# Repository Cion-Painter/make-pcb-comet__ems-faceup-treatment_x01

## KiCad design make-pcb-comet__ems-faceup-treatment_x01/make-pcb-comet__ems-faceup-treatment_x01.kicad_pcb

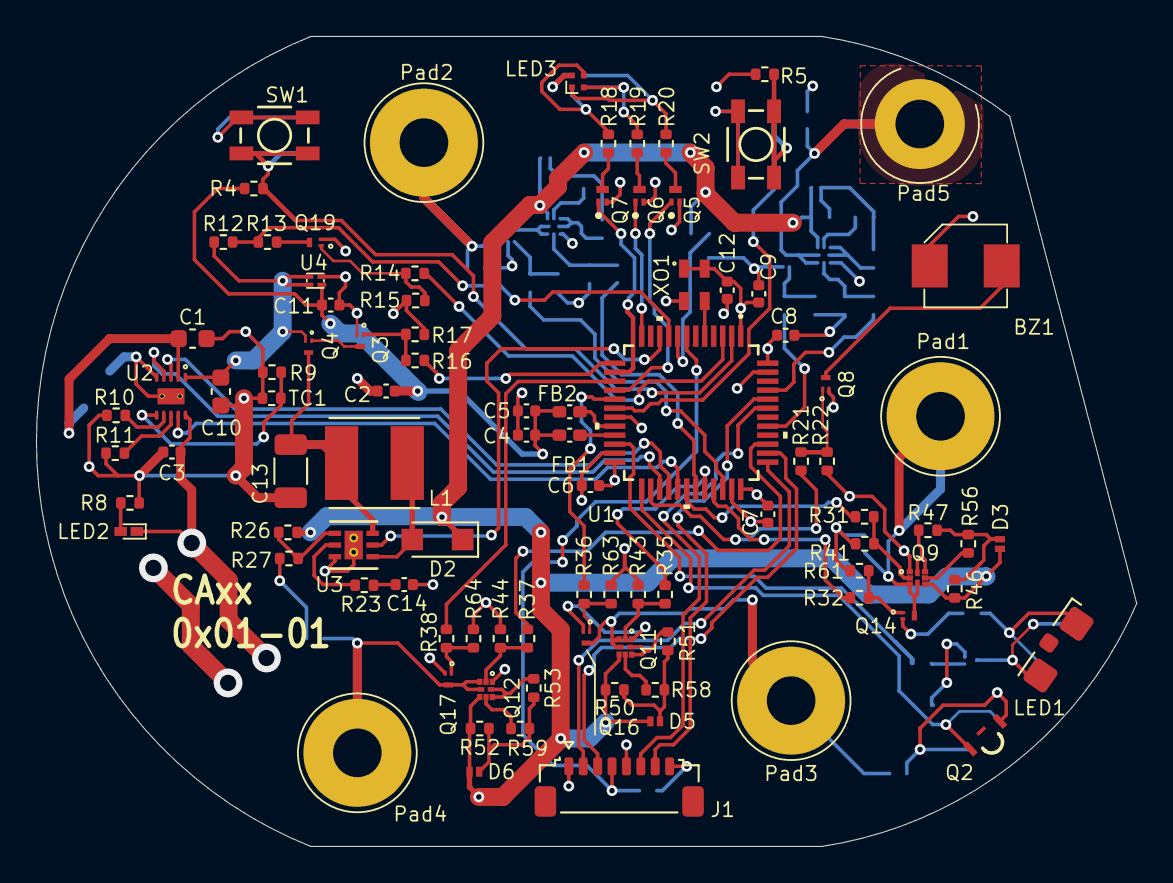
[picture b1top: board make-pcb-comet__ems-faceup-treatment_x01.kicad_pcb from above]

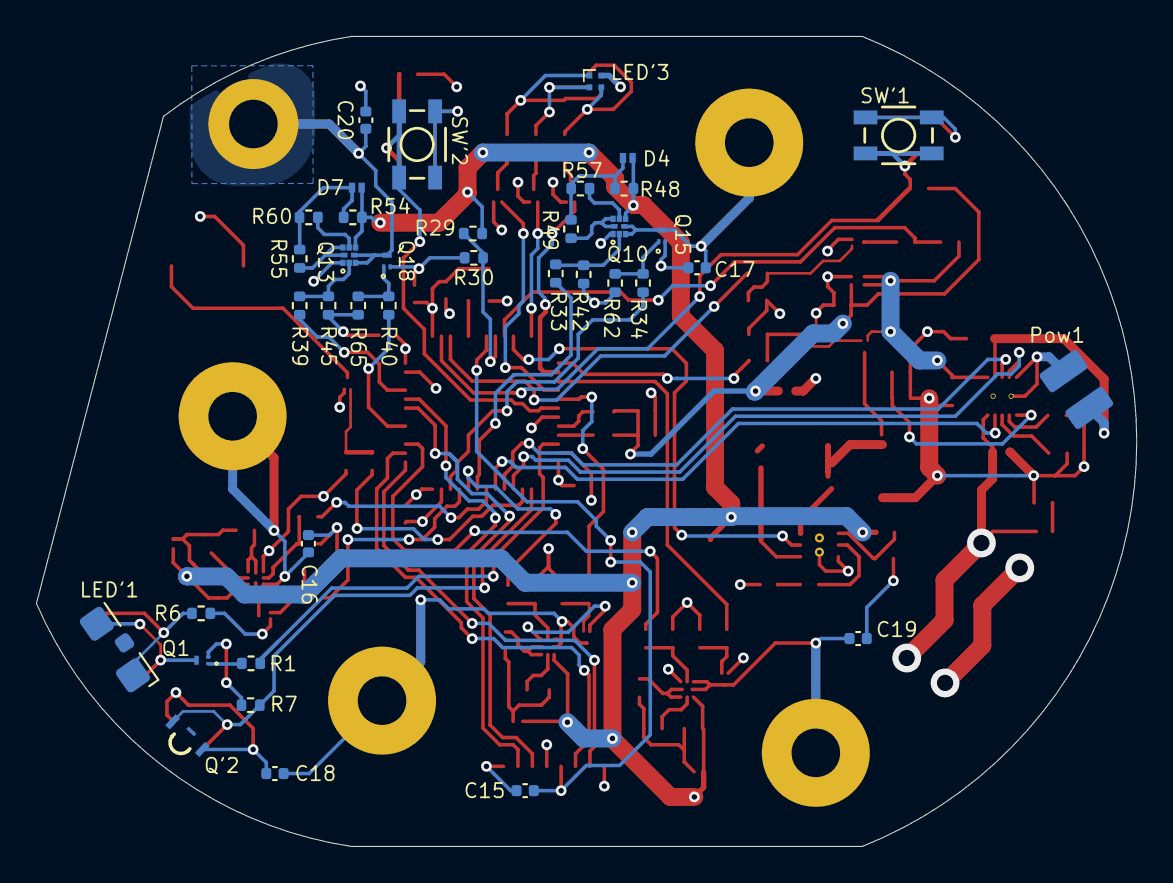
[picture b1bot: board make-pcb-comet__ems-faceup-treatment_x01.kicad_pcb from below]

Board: 4 copper layers, 61.1 x 45.0 mm, 132 parts (38 on the bottom side), 94 nets.

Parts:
BZ1: OWMB-404020SA-40-17; 4.0x4.0 SP OWMB-404020SA
C1: 4.7uF; C_0603_1608Metric
C2: 4.7uF; C_0402_1005Metric
C3, C9, C11: 1uF; C_0402_1005Metric
C4, C5, C6, C7, C8, C12, C15, C16, C17, C18, C19, C20: 0.1uF; C_0402_1005Metric
C10: 10uF; C_0603_1608Metric
C13: 10uF; C_1206_3216Metric
C14: 33nF; C_0402_1005Metric
D2: SS16FP; Nexperia_CFP3_SOD-123W
D3, D4, D5, D6, D7: PZU5.1BL; SOD-882_TOS
FB1, FB2: BLM15AG601SN1D; L_0402_1005Metric_Pad0.77x0.64mm_HandSolder
J1: SUH_Connector_side_08-pin; JST_SUR_SM08B-SURS-TF_1x08-1MP_P0.80mm_Horizontal
L1: LQH5BPN100MT0L; IND_LQH5BPN100MT0L
LED1: KPA-3010F3C; LED_Kingbright_KPA-3010_3x2x1mm
LED2: KPHHS-1005SURCK; LED_APHHS1005
LED3: UHD111A-FKA-C3K23E1L3VG5ZB3Z3; SMD4_UHD111A-FKA_CRW
LED'1: LED_Kingbright_KPA-3010_3x2x1mm
LED'3: UHD111A-FKA-C3K23E1L3VG5ZB3Z3; SMD4_UHD111A-FKA_CRW
Pad1, Pad2, Pad3, Pad4, Pad5: Pad 6 _ Hole 3.5
Pow1: LiPo 3.2 x 1.7
Q1, Q4: CSD25483F4; YJC0003A_TEX
Q2: 1541021NCA170; WL-STSB_1002
Q3, Q8, Q14, Q15, Q16, Q17, Q18, Q19: RV2E014AJ; DFN1006
Q5, Q6, Q7: DDTC143ZLP; DFN101X61X53-3N
Q9, Q10, Q11, Q12, Q13: PMCXB1000UE; TRANS_PMDXB600UNEZ
Q'2: 1541021NCA170; WL-STSB_1002
R1, R14, R16, R21, R31, R32, R33, R34, R35, R36, R37, R38, R39, R40, R47, R49, R51, R53, R55: 100; R_0402_1005Metric
R4, R5, R7: 51k; R_0402_1005Metric
R6: 68; R_0402_1005Metric
R8: 470; R_0402_1005Metric
R9, R12: 10k; R_0402_1005Metric
R10, R13: 3.3k; R_0402_1005Metric
R11: 33k; R_0402_1005Metric
R15, R17, R22, R41, R42, R43, R44, R45, R61, R62, R63, R64, R65: 100k; R_0402_1005Metric
R18, R19, R20: 300; R_0402_1005Metric
R23: 36.5k; R_0402_1005Metric
R26: 187k; R_0402_1005Metric
R27: 10.5k; R_0402_1005Metric
R29: 510k; R_0402_1005Metric
R30: 62k; R_0402_1005Metric
R46, R48, R50, R52, R54: 47k; R_0402_1005Metric
R56, R57, R58, R59, R60: 22; R_0402_1005Metric
SW1, SW2: EVPAA; SW_EVP-AA102K_PAN
SW'1, SW'2: EVPAA; SW_EVP-AA102K_PAN
TC1: NTC; R_0402_1005Metric
U1: STM32G431C6T6; LQFP48-7x7mm
U2: BQ25185DLHR; IC_BQ25185DLHR
U3: TPS61170DRVRG4; 6-WDFN_roshutsu_DRV6_1P6X1
U4: XC6504A3317R-G; USPN-4B02
XO1: SG2016CAN20.0000M-TJGA3; SMT_M-TJGA3_EPS

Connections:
+USB_5V0: C3.1, LED2.1 (Anode), U2.10 (IN)
/BAT_VOL: R12.2, R13.2, U1.9 (PA1)
/Buzz: R21.2, U1.26 (PB12)
/EMC_Pow: R16.1, U1.13 (PA5)
/EMS(1)_H: R31.1, U1.30 (PA8)
/EMS(1)_L: R32.1, U1.33 (PA11)
/EMS(2)_H: R33.1, U1.31 (PA9)
/EMS(2)_L: R34.1, U1.34 (PA12)
/EMS(3)_H: R35.1, U1.32 (PA10)
/EMS(3)_L: R36.1, U1.17 (PB1)
/EMS(4)_H: R37.1, U1.39 (PA15)
/EMS(4)_L: R38.1, U1.15 (PA7)
/EMS(5)_H: R39.1, U1.45 (PB8-BOOT0)
/EMS(5)_L: R40.1, U1.41 (PB4)
/EMS_POW: R29.1, R30.2, U1.8 (PA0)
/EMS_POW_PWM: U1.10 (PA2), U3.5 (CTRL)
/EMS_SW: R4.1, SW1.3 (K), SW1.4 (A), SW'1.3 (K), SW'1.4 (A), U1.2 (PC13)
/IrD_RX: Q2.1 (C), Q'2.1 (C), R7.1, U1.25 (PB11)
/IrD_TX: R1.1, U1.22 (PB10)
/LEDB: Q5.1 (B), U1.16 (PB0)
/LEDG: Q6.1 (B), U1.12 (PA4)
/LEDR: Q7.1 (B), U1.14 (PA6)
/RESET_SW: C15.2, J1.4, U1.7 (PG10-NRST)
/SW1: R5.1, SW2.3 (K), SW2.4 (A), SW'2.3 (K), SW'2.4 (A), U1.18 (PB2)
/SWCLK: J1.3, U1.38 (PA14)
/SWDIO: J1.2, U1.37 (PA13)
/UART1_RX: J1.7, U1.44 (PB7)
/UART1_TX: J1.6, U1.43 (PB6)
EMS_Pow_20V: D2.1 (K), D3.1 (Cathode), D4.1 (Cathode), D5.1 (Cathode), D6.1 (Cathode), D7.1 (Cathode), Q9.4 (Source2), Q10.4 (Source2), Q11.4 (Source2), Q12.4 (Source2), Q13.4 (Source2), R26.2, R29.2, R46.2, R48.2, R50.2, R52.2, R54.2
GNDPWR: C1.2, C2.1, C3.2, C4.1, C5.1, C6.1, C7.1, C8.1, C9.1, C10.2, C11.2, C12.1, C13.2, C14.2, C15.1, C16.1, C17.1, C18.1, C19.1, C20.1, J1.1, J1.8, Pow1.2 (-), Q2.2 (E), Q3.2 (Source), Q5.2 (E), Q6.2 (E), Q7.2 (E), Q8.2 (Source), Q9.1 (Source1), Q10.1 (Source1), Q11.1 (Source1), Q12.1 (Source1), Q13.1 (Source1), Q14.2 (Source), Q15.2 (Source), Q16.2 (Source), Q17.2 (Source), Q18.2 (Source), Q19.2 (Source), Q'2.2 (E), R6.1, R8.2, R9.2, R10.2, R11.2, R15.2, R17.1, R22.1, R27.1, R30.1, R41.1, R42.1, R43.1, R44.1, R45.1, R61.1, R62.1, R63.1, R64.1, R65.1, SW1.1, SW1.2, SW2.1, SW2.2, SW'1.1, SW'1.2, SW'2.1, SW'2.2, TC1.1, U1.19 (VSSA), U1.23 (VSS), U1.35 (VSS), U1.47 (VSS), U2.5 (GND), U2.11 (THERMAL_PAD), U2.12, U2.13, U3.3 (GND), U3.7 (EPAD), U3.V, U4.2 (GND), XO1.2 (GND)
unnamed: BZ1.2 (-), Q8.3 (Drain)
unnamed: C14.1, R23.2
unnamed: D2.2 (A), L1.2, U3.4 (SW)
unnamed: D3.2 (Anode), R46.1, R47.2, R56.1
unnamed: D4.2 (Anode), R48.1, R49.2, R57.1
unnamed: D5.2 (Anode), R50.1, R51.2, R58.1
unnamed: D6.2 (Anode), R52.1, R53.2, R59.1
unnamed: D7.2 (Anode), R54.1, R55.2, R60.1
unnamed: LED2.2 (Cathode), R8.1
unnamed: LED1.2 (Anode), LED'1.2 (Anode), Q1.3 (Drain)
unnamed: LED1.1 (Cathode), LED'1.1 (Cathode), R6.2
unnamed: LED3.1, LED'3.1, R20.1
unnamed: LED3.2, LED'3.2, R19.2
unnamed: LED3.3, LED'3.3, R18.2
unnamed: C1.1, Pow1.1 (+), U2.2 (BAT)
unnamed: Q1.1 (Gate), R1.2
unnamed: Q3.3 (Drain), Q4.1 (Gate)
unnamed: Q3.1 (Gate), R16.2, R17.2
unnamed: C13.1, L1.1, Q4.3 (Drain), U3.6 (VIN)
unnamed: Q5.3 (C), R20.2
unnamed: Q6.3 (C), R19.1
unnamed: Q7.3 (C), R18.1
unnamed: Q8.1 (Gate), R21.1, R22.2
unnamed: Q9.6 (Drain1), Q9.7 (Drain1), R47.1
unnamed: Q9.2 (Gate1), R31.2, R41.2
unnamed: Q9.5 (Gate2), R56.2
unnamed: Q10.6 (Drain1), Q10.7 (Drain1), R49.1
unnamed: Q10.2 (Gate1), R33.2, R42.2
unnamed: Q10.5 (Gate2), R57.2
unnamed: Q11.6 (Drain1), Q11.7 (Drain1), R51.1
unnamed: Q11.2 (Gate1), R35.2, R43.2
unnamed: Q11.5 (Gate2), R58.2
unnamed: Q12.6 (Drain1), Q12.7 (Drain1), R53.1
unnamed: Q12.2 (Gate1), R37.2, R44.2
unnamed: Q12.5 (Gate2), R59.2
unnamed: Q13.6 (Drain1), Q13.7 (Drain1), R55.1
unnamed: Q13.2 (Gate1), R39.2, R45.2
unnamed: Q13.5 (Gate2), R60.2
unnamed: C16.2, Pad1.1 (1_1), Q9.3 (Drain2), Q9.8 (Drain2), Q14.3 (Drain)
unnamed: Q14.1 (Gate), R32.2, R61.2
unnamed: C17.2, Pad2.1 (1_1), Q10.3 (Drain2), Q10.8 (Drain2), Q15.3 (Drain)
unnamed: Q15.1 (Gate), R34.2, R62.2
unnamed: C18.2, Pad3.1 (1_1), Q11.3 (Drain2), Q11.8 (Drain2), Q16.3 (Drain)
unnamed: Q16.1 (Gate), R36.2, R63.2
unnamed: C19.2, Pad4.1 (1_1), Q12.3 (Drain2), Q12.8 (Drain2), Q17.3 (Drain)
unnamed: Q17.1 (Gate), R38.2, R64.2
unnamed: C20.2, Pad5.1 (1_1), Q13.3 (Drain2), Q13.8 (Drain2), Q18.3 (Drain)
unnamed: Q18.1 (Gate), R40.2, R65.2
unnamed: Q19.3 (Drain), R13.1
unnamed: Q19.1 (Gate), R14.1, R15.1
unnamed: U1.27 (PB13), U2.4 (~CE)
unnamed: U1.28 (PB14), U2.3 (STAT2)
unnamed: U1.29 (PB15), U2.9 (STAT1)
unnamed: R14.2, U1.3 (PC14-OSC32_IN)
unnamed: U1.5 (PF0-OSC_IN), XO1.3 (OUT)
unnamed: FB1.2, U1.21 (VDDA)
unnamed: FB2.2, U1.20 (VREF+)
unnamed: R10.1, U2.7 (ILIM/VSET)
unnamed: R11.1, U2.8 (ISET)
unnamed: R9.1, TC1.2, U2.6 (TS/MR)
unnamed: R23.1, U3.2 (COMP)
unnamed: R26.1, R27.2, U3.1 (FB)
U2_LDO+3.3V: BZ1.1 (+), C2.2, C4.2, C5.2, C6.2, C7.2, C8.2, C9.2, C11.1, C12.2, FB1.1, FB2.1, J1.5, LED3.4, LED'3.4, Q1.2 (Source), R4.2, R5.2, R7.2, U1.1 (VBAT), U1.24 (VDD), U1.36 (VDD), U1.48 (VDD), U4.1 (VOUT), XO1.1 (~ST), XO1.4 (Vcc)
U2_SYS_+BAT: C10.1, Q4.2 (Source), R12.1, U2.1 (SYS), U4.3 (EN), U4.4 (VIN)
